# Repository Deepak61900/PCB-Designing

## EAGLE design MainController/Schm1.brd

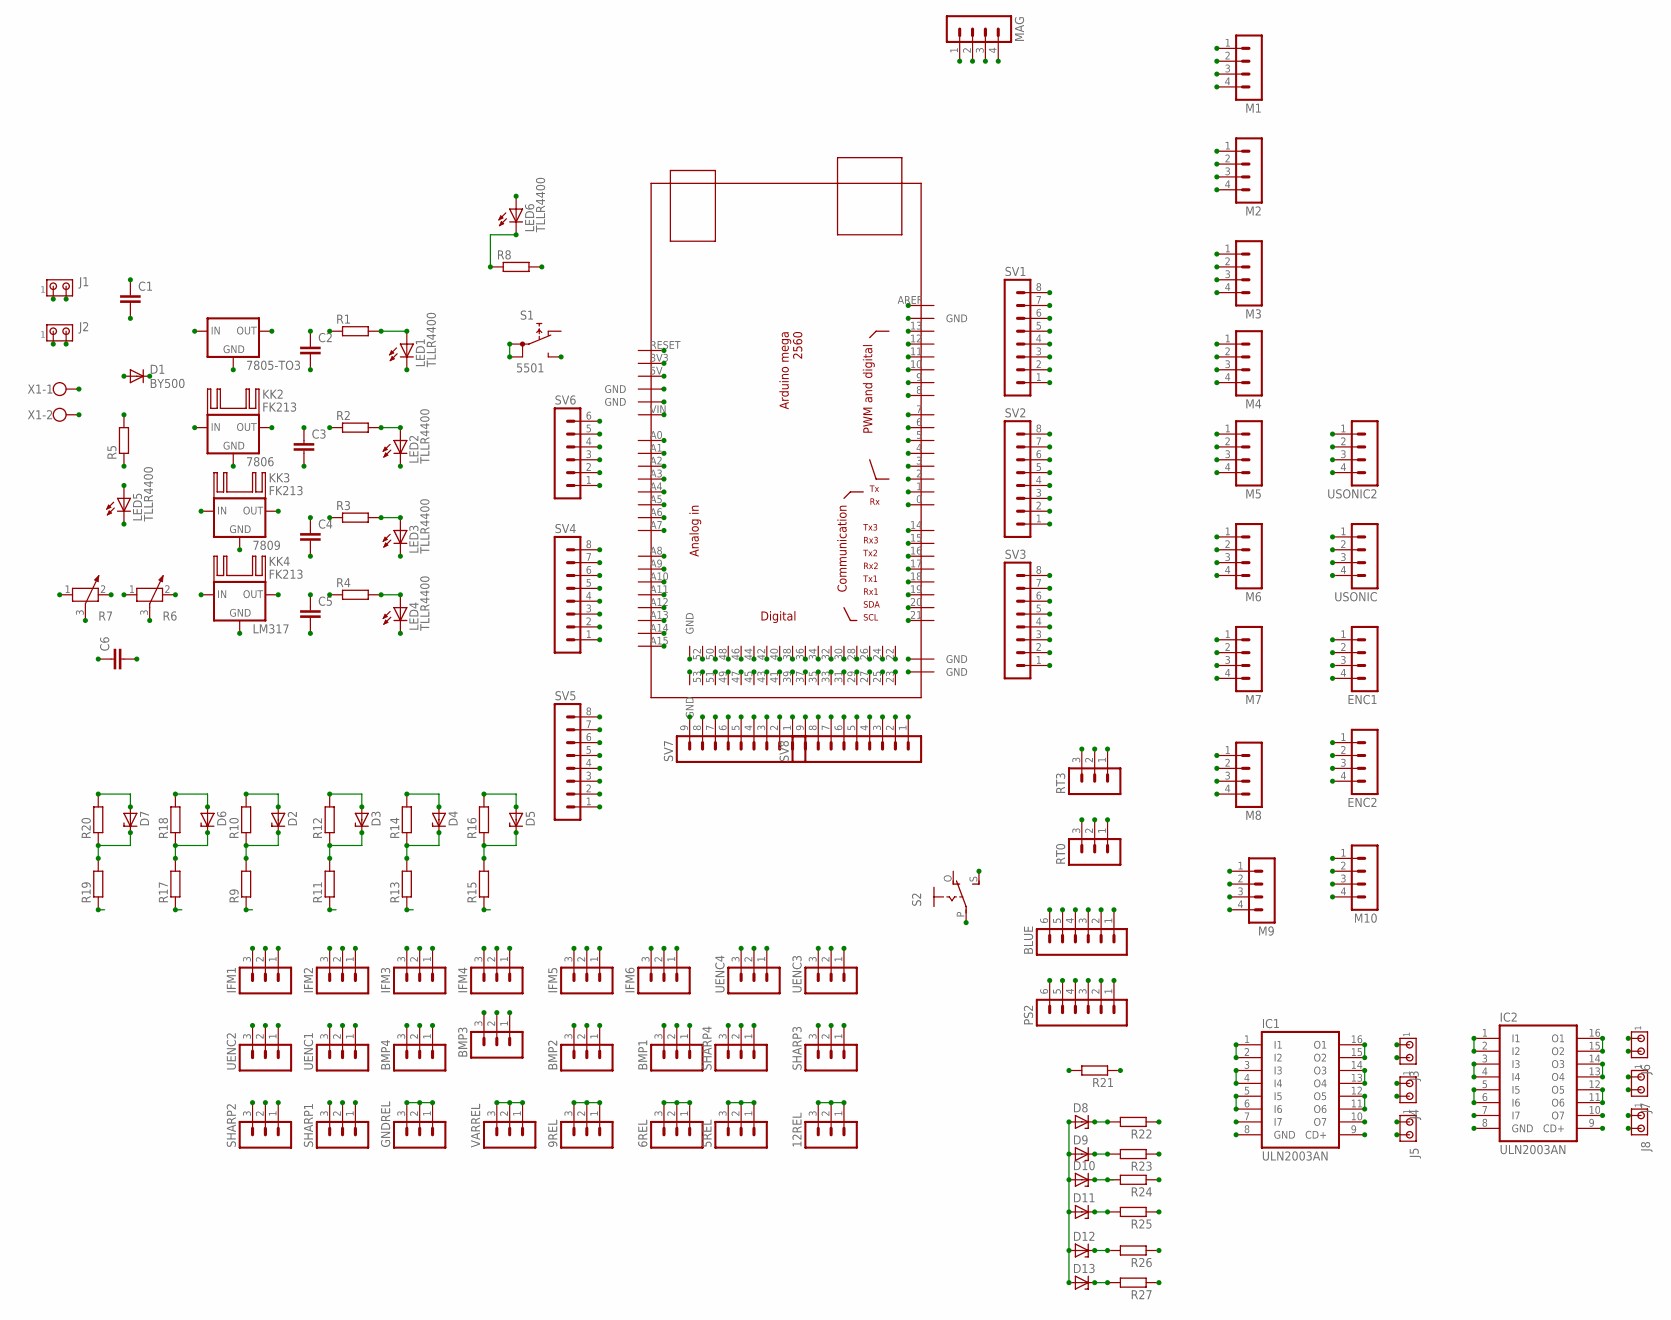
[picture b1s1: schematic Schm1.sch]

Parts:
5REL, 6REL, 9REL, 12REL: MA03-1
7805-TO3: 78XX-TO3; TO3-78
7806, 7809: 78XXS
BLUE: MA06-1
BMP1, BMP2, BMP3, BMP4: MA03-1
C1: C-EU075-063X106; C075-063X106
C2, C3, C4, C5, C6: C-EU050-075X075; C050-075X075
D1: BY500; DO201-15
D2, D3, D4, D5, D6, D7, D8, D9, D10, D11, D12, D13: ZENER-DIODEDO34-7; DO34Z7
ENC1, ENC2: MA04-1
GNDREL: MA03-1
IC1, IC2: ULN2003AN; DIL16
IFM1, IFM2, IFM3, IFM4, IFM5, IFM6: MA03-1
J1, J2: MTA02-156; 1X2MTA
J3, J4, J5, J6, J7, J8: MTA02-100; 10X02MTA
KK2, KK3, KK4: FK213
LED1, LED2, LED3, LED4, LED5, LED6: TLLR4400; LED3MM
LM317: 78XXS
M1, M2, M3, M4, M5, M6, M7, M8, M9, M10: MA04-1
MAG: MA04-1
PS2: MA06-1
R1, R2, R3, R4, R5, R8, R9, R10, R11, R12, R13, R14, R15, R16, R17, R18, R19, R20, R21, R22, R23, R24, R25, R26, R27: R-EU_0207/10; 0207/10
R6, R7: POTENTIOMETER_PT-10; PT-10
RT0, RT3: MA03-1
S1: 5501
S2: EG1218S; EG1218
SHARP1, SHARP2, SHARP3, SHARP4: MA03-1
SV1, SV2, SV3, SV4, SV5: MA08-1
SV6: MA06-1
SV7, SV8: MA09-1
U$1: MEGA_DEVICE; MEGABOX
UENC1, UENC2, UENC3, UENC4: MA03-1
USONIC, USONIC2: MA04-1
VARREL: MA03-1
X1: W237-102

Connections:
0: RT0.2, SV2.1, U$1.0
1: RT0.3, SV2.2, U$1.1
2: ENC1.1, SV2.3, U$1.2, UENC1.3
3: ENC1.2, SV2.4, U$1.3, UENC2.3
3V3: MAG.2, SV6.5, U$1.3V3
4: M1.1, SV2.5, U$1.4
5: M6.1, SV2.6, U$1.5
5OUT: 5REL.1, 5REL.2, 5REL.3, 7805-TO3.1 (OUT), BLUE.3, BMP1.2, BMP2.2, BMP3.2, BMP4.2, C2.1, ENC1.3, ENC2.3, PS2.2, R1.1, R21.1, SHARP1.1, SHARP2.1, SHARP3.1, SHARP4.1, UENC1.2, UENC2.2, UENC3.2, UENC4.2, USONIC.4, USONIC2.4
6: M7.1, SV2.7, U$1.6
6OUT: 6REL.1, 6REL.2, 6REL.3, 7806.OUT, C3.1, R2.1
7: M8.1, SV2.8, U$1.7
8: M9.1, SV1.1, U$1.8
9: M10.1, SV1.2, U$1.9
10: M5.1, SV1.3, U$1.10
11: M4.1, SV1.4, U$1.11
12: M3.1, SV1.5, U$1.12
12IN: 7805-TO3.2 (IN), 7806.IN, 7809.IN, C6.1, D1.C, LM317.IN
12V: 12REL.1, 12REL.2, 12REL.3, C1.1, D1.A, IC1.9 (CD+), IC2.9 (CD+), IFM1.2, IFM2.2, IFM3.2, IFM4.2, IFM5.2, IFM6.2, J1.1, J2.1, J3.1, J4.1, J5.1, J6.1, J7.1, J8.1, R5.2, X1.1
13: M2.1, SV1.6, U$1.13
14: RT3.3, SV3.8, U$1.14
15: RT3.2, SV3.7, U$1.15
16: BLUE.5, SV3.6, U$1.16
17: BLUE.4, SV3.5, U$1.17
18: ENC2.1, SV3.4, U$1.18, UENC3.3
19: ENC2.2, SV3.3, U$1.19, UENC4.3
20: MAG.3, SV3.2, U$1.20
21: MAG.4, SV3.1, U$1.21
22: M1.2, U$1.22
23: M1.3, SV8.2, U$1.23
24: M2.2, U$1.24
25: M6.2, SV8.3, U$1.25
26: M2.3, U$1.26
27: M6.3, SV8.4, U$1.27
28: M3.2, U$1.28
29: M7.2, SV8.5, U$1.29
30: M3.3, U$1.30
31: M7.3, SV8.6, U$1.31
32: M4.2, U$1.32
33: M8.2, SV8.7, U$1.33
34: M4.3, U$1.34
35: M8.3, SV8.8, U$1.35
36: M5.2, U$1.36
37: M9.2, SV8.9, U$1.37
38: M5.3, U$1.38
39: M9.3, SV7.1, U$1.39
40: BMP4.3, U$1.40
41: D11.C, R25.2, SV7.2, U$1.41
42: BMP2.3, U$1.42
43: D12.C, R26.2, SV7.3, U$1.43
44: BMP1.3, U$1.44
45: D13.C, R27.2, SV7.4, U$1.45
46: BMP3.3, U$1.46
47: PS2.6, SV7.5, U$1.47
48: D10.C, R24.2, U$1.48
49: PS2.5, SV7.6, U$1.49
50: D9.C, R23.2, U$1.50
51: PS2.4, SV7.7, U$1.51
52: D8.C, R22.2, U$1.52
53: PS2.3, R21.2, SV7.8, U$1.53
A0: M10.3, SV4.8, U$1.A0
A1: M10.2, SV4.7, U$1.A1
A2: SHARP1.3, SV4.6, U$1.A2
A3: SHARP2.3, SV4.5, U$1.A3
A4: SHARP3.3, SV4.4, U$1.A4
A5: SHARP4.3, SV4.3, U$1.A5
A6: SV4.2, U$1.A6, USONIC.3
A7: SV4.1, U$1.A7, USONIC.2
A8: SV5.8, U$1.A8, USONIC2.3
A9: SV5.7, U$1.A9, USONIC2.2
A10: D7.C, R19.2, R20.1, SV5.6, U$1.A10
A11: D6.C, R17.2, R18.1, SV5.5, U$1.A11
A12: D2.C, R9.2, R10.1, SV5.4, U$1.A12
A13: D3.C, R11.2, R12.1, SV5.3, U$1.A13
A14: D4.C, R13.2, R14.1, SV5.2, U$1.A14
A15: D5.C, R15.2, R16.1, SV5.1, U$1.A15
AREF: SV1.8, U$1.AREF
B3V3: BLUE.2, S2.P
DIN: LED5.A, R5.1
GND: 7805-TO3.3 (GND), 7806.GND, 7809.GND, BLUE.1, BMP1.1, BMP2.1, BMP3.1, BMP4.1, C1.2, C2.2, C3.2, C4.2, C5.2, C6.2, D2.A, D3.A, D4.A, D5.A, D6.A, D7.A, D8.A, D9.A, D10.A, D11.A, D12.A, D13.A, ENC1.4, ENC2.4, GNDREL.1, GNDREL.2, GNDREL.3, IC1.8 (GND), IC2.8 (GND), IFM1.1, IFM2.1, IFM3.1, IFM4.1, IFM5.1, IFM6.1, J1.2, J2.2, LED1.K (C), LED2.K (C), LED3.K (C), LED4.K (C), LED5.K (C), M1.4, M2.4, M3.4, M4.4, M5.4, M6.4, M7.4, M8.4, M9.4, M10.4, MAG.1, PS2.1, R7.3, R8.2, R10.2, R12.2, R14.2, R16.2, R18.2, R20.2, RT0.1, RT3.1, S1.NO, SHARP1.2, SHARP2.2, SHARP3.2, SHARP4.2, SV1.7, SV6.2, SV6.3, SV7.9, U$1.GND@1 (GND), U$1.GND@2 (GND), U$1.GND@3 (GND), U$1.GND@6 (GND), U$1.GND@7 (GND), UENC1.1, UENC2.1, UENC3.1, UENC4.1, USONIC.1, USONIC2.1, X1.2
JOK1: LM317.GND, R6.3, R7.1
KEY: BLUE.6, S2.S
unnamed: LED6.K (C), R8.1
unnamed: LED4.A, R4.2
unnamed: LED3.A, R3.2
unnamed: LED2.A, R2.2
unnamed: LED1.A, R1.2
PN1: IC1.15 (O2), IC1.16 (O1), J3.2
PN2: IC1.13 (O4), IC1.14 (O3), J4.2
PN3: IC1.11 (O6), IC1.12 (O5), J5.2
PN4: IC2.15 (O2), IC2.16 (O1), J6.2
PN5: IC2.13 (O4), IC2.14 (O3), J7.2
PN6: IC2.11 (O6), IC2.12 (O5), J8.2
RESET: S1.1A, S1.1B, SV6.6, U$1.RESET
S1: IFM1.3, R19.1
S2: IFM2.3, R17.1
S3: IFM3.3, R9.1
S4: IFM4.3, R11.1
S5: IFM5.3, R13.1
S6: IFM6.3, R15.1
U1: IC1.5 (I5), IC1.6 (I6), R22.1
U2: IC1.3 (I3), IC1.4 (I4), R23.1
U3: IC1.1 (I1), IC1.2 (I2), R24.1
U4: IC2.5 (I5), IC2.6 (I6), R25.1
U5: IC2.3 (I3), IC2.4 (I4), R26.1
U6: IC2.1 (I1), IC2.2 (I2), R27.1
VAROUT: C5.1, LM317.OUT, R4.1, R6.1, VARREL.1, VARREL.2, VARREL.3
VCC: LED6.A, SV6.4, SV8.1, U$1.5V, U$1.GND@4 (GND), U$1.GND@5 (GND)
VIN: 9REL.1, 9REL.2, 9REL.3, 7809.OUT, C4.1, R3.1, SV6.1, U$1.VIN

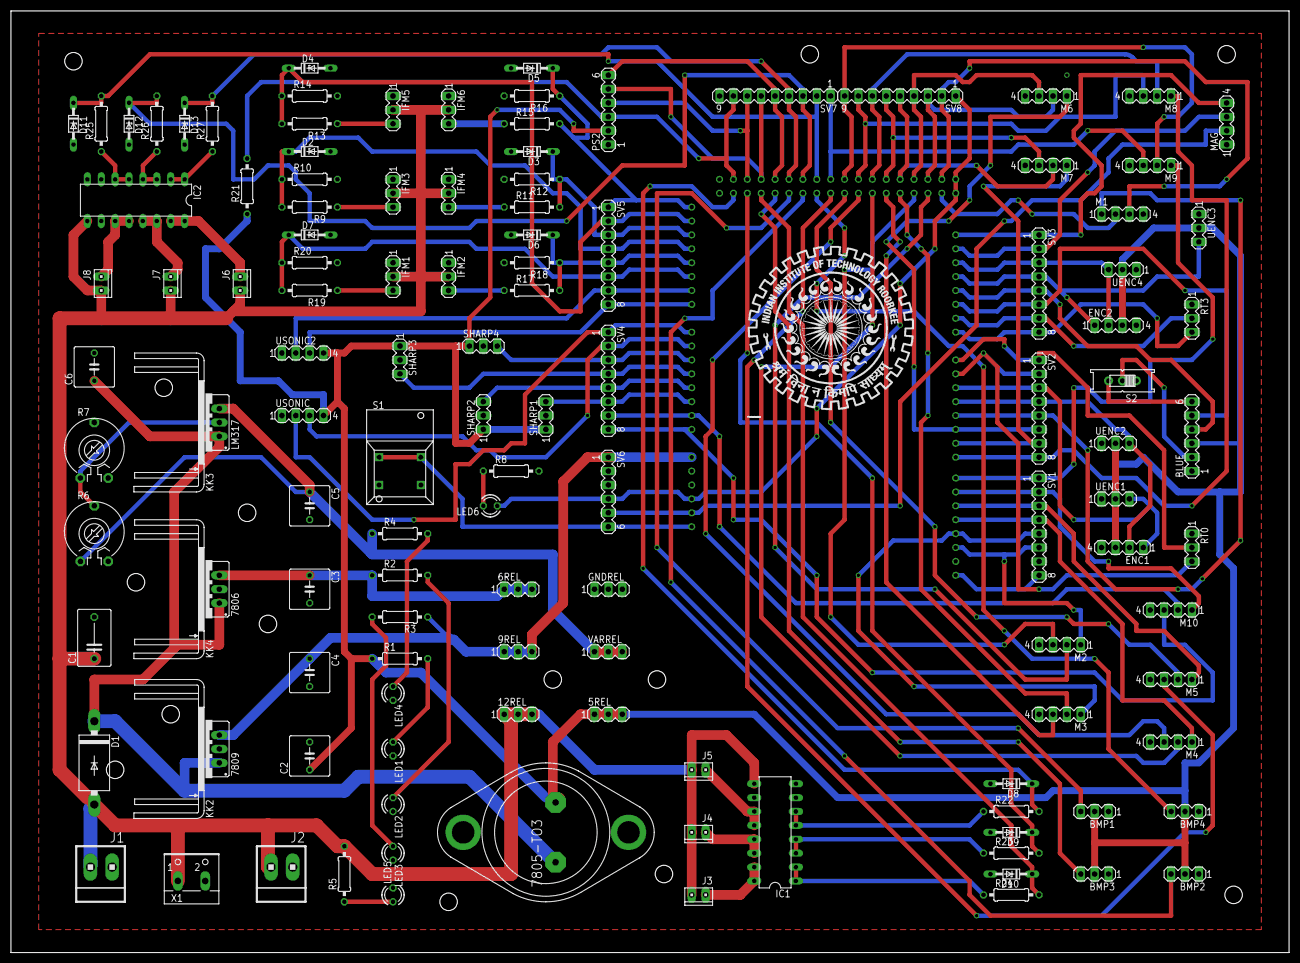
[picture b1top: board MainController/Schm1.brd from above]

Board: 2 copper layers, 233.7 x 172.1 mm, 125 parts (1 on the bottom side), 108 nets.

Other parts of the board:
U$2: IITR_2

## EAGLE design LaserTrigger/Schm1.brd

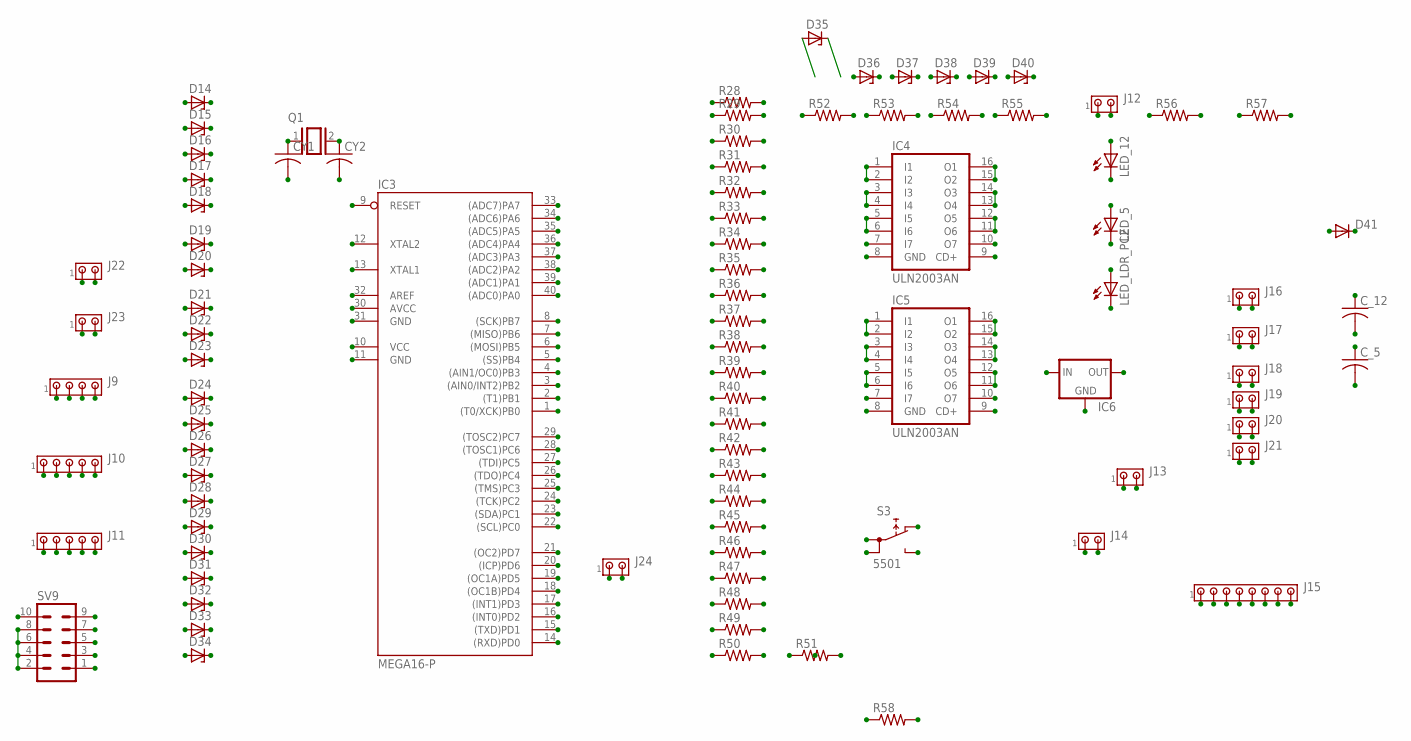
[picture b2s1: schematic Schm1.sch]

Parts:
CY1, CY2: C-US050-024X044; C050-024X044
C_5, C_12: C-US050-075X075; C050-075X075
D14, D15, D16, D17, D18, D19, D20, D21, D22, D23, D24, D25, D26, D27, D28, D29, D30, D31, D32, D33, D34, D35, D36, D37, D38, D39, D40: ZENER-DIODEDO34-7; DO34Z7
D41: DIODE-DO201-15; DO201-15
IC3: MEGA16-P; DIL40
IC4, IC5: ULN2003AN; DIL16
IC6: 78XX-TO3; TO3-78
J9: MTA04-100; 10X04MTA
J10, J11: MTA05-100; 10X05MTA
J12, J13, J23: MTA02-156; 1X2MTA
J14, J16, J17, J18, J19, J20, J21, J22, J24: MTA02-100; 10X02MTA
J15: MTA08-100; 10X08MTA
LED_5, LED_12: LED3MM
LED_LDR_PC2: LED3MM
Q1: XTAL/S; QS
R28, R29, R30, R31, R32, R33, R34, R35, R36, R37, R38, R39, R40, R41, R42, R43, R44, R45, R46, R47, R48, R49, R50, R51, R52, R53, R54, R55, R56, R57, R58: R-US_0207/7; 0207/7
S3: 5501
SV9: MA05-2

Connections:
12V1: C_12.1, D41.C, IC4.9 (CD+), IC5.9 (CD+), IC6.2 (IN), J12.1, J16.2, J17.2, J18.2, J19.2, J20.2, J21.2, J22.1, R28.2, R29.2, R30.2, R31.2, R32.2, R33.2, R34.2, R35.2, R36.2, R37.2, R38.2, R39.2, R40.2, R41.2, R42.2, R43.2, R44.2, R45.2, R46.2, R47.2, R48.2, R49.2
AREF1: IC3.32 (AREF)
D: D41.A, J23.1
GND1: CY1.2, CY2.2, C_5.2, C_12.2, D14.A, D15.A, D16.A, D17.A, D18.A, D19.A, D20.A, D21.A, D22.A, D23.A, D24.A, D25.A, D26.A, D27.A, D28.A, D29.A, D30.A, D31.A, D32.A, D33.A, D34.A, D35.A, D36.A, D37.A, D38.A, D39.A, D40.A, IC3.11 (GND), IC3.31 (GND), IC4.8 (GND), IC5.8 (GND), IC6.3 (GND), J9.4, J12.2, J13.2, J14.2, J22.2, J23.2, LED_5.K (C), LED_12.K (C), LED_LDR_PC2.K (C), S3.NO, SV9.2, SV9.4, SV9.6, SV9.8
LED1: LED_12.A, R49.1
LED2: LED_5.A, R50.1
LED3: LED_LDR_PC2.A, R51.2
N1: IC4.15 (O2), IC4.16 (O1), J16.1
N2: IC4.13 (O4), IC4.14 (O3), J17.1
N3: IC4.11 (O6), IC4.12 (O5), J18.1
N4: IC5.15 (O2), IC5.16 (O1), J19.1
N5: IC5.13 (O4), IC5.14 (O3), J20.1
N6: IC5.11 (O6), IC5.12 (O5), J21.1
PA0: D34.C, IC3.40 ((ADC0)PA0), J15.1, R48.1
PA1: D33.C, IC3.39 ((ADC1)PA1), J15.2, R47.1
PA2: D32.C, IC3.38 ((ADC2)PA2), J15.3, R46.1
PA3: D31.C, IC3.37 ((ADC3)PA3), J15.4, R45.1
PA4: D30.C, IC3.36 ((ADC4)PA4), J15.5, R44.1
PA5: D29.C, IC3.35 ((ADC5)PA5), J15.6, R43.1
PA6: D28.C, IC3.34 ((ADC6)PA6), J15.7, R42.1
PA7: D27.C, IC3.33 ((ADC7)PA7), J15.8, R41.1
PB0: D14.C, IC3.1 ((T0/XCK)PB0), J10.1, R28.1
PB1: D15.C, IC3.2 ((T1)PB1), J10.2, R29.1
PB2: D16.C, IC3.3 ((AIN0/INT2)PB2), J10.3, R30.1
PB3: D17.C, IC3.4 ((AIN1/OC0)PB3), J10.4, R31.1
PB4: D18.C, IC3.5 ((SS)PB4), J10.5, R32.1
PB5: IC3.6 ((MOSI)PB5), SV9.9
PB6: IC3.7 ((MISO)PB6), SV9.1
PB7: IC3.8 ((SCK)PB7), SV9.3
PC0: D25.C, IC3.22 ((SCL)PC0), J9.2, R39.1
PC1: D26.C, IC3.23 ((SDA)PC1), J9.1, R40.1
PC2: D40.C, IC3.24 ((TCK)PC2), R51.1, R57.1
PC3: D39.C, IC3.25 ((TMS)PC3), R56.1
PC4: D38.C, IC3.26 ((TDO)PC4), R55.1
PC5: D37.C, IC3.27 ((TDI)PC5), R54.1
PC6: D36.C, IC3.28 ((TOSC1)PC6), R53.1
PC7: D35.C, IC3.29 ((TOSC2)PC7), R52.1
PD0: IC3.14 ((RXD)PD0), J24.1
PD1: IC3.15 ((TXD)PD1), J24.2
PD2: D19.C, IC3.16 ((INT0)PD2), J11.1, R33.1
PD3: D20.C, IC3.17 ((INT1)PD3), J11.2, R34.1
PD4: D21.C, IC3.18 ((OC1B)PD4), J11.3, R35.1
PD5: D22.C, IC3.19 ((OC1A)PD5), J11.4, R36.1
PD6: D23.C, IC3.20 ((ICP)PD6), J11.5, R37.1
PD7: D24.C, IC3.21 ((OC2)PD7), J9.3, R38.1
RESET1: IC3.9 (RESET), R58.2, S3.1A, S3.1B, SV9.5
U7: IC4.1 (I1), IC4.2 (I2), R52.2
U8: IC4.3 (I3), IC4.4 (I4), R53.2
U9: IC4.5 (I5), IC4.6 (I6), R54.2
U10: IC5.1 (I1), IC5.2 (I2), R55.2
U11: IC5.3 (I3), IC5.4 (I4), R56.2
U12: IC5.5 (I5), IC5.6 (I6), R57.2
VCC1: C_5.1, IC3.10 (VCC), IC3.30 (AVCC), IC6.1 (OUT), J13.1, J14.1, R50.2, R58.1, SV9.10
XTAL1: CY1.1, IC3.13 (XTAL1), Q1.1
XTAL2: CY2.1, IC3.12 (XTAL2), Q1.2

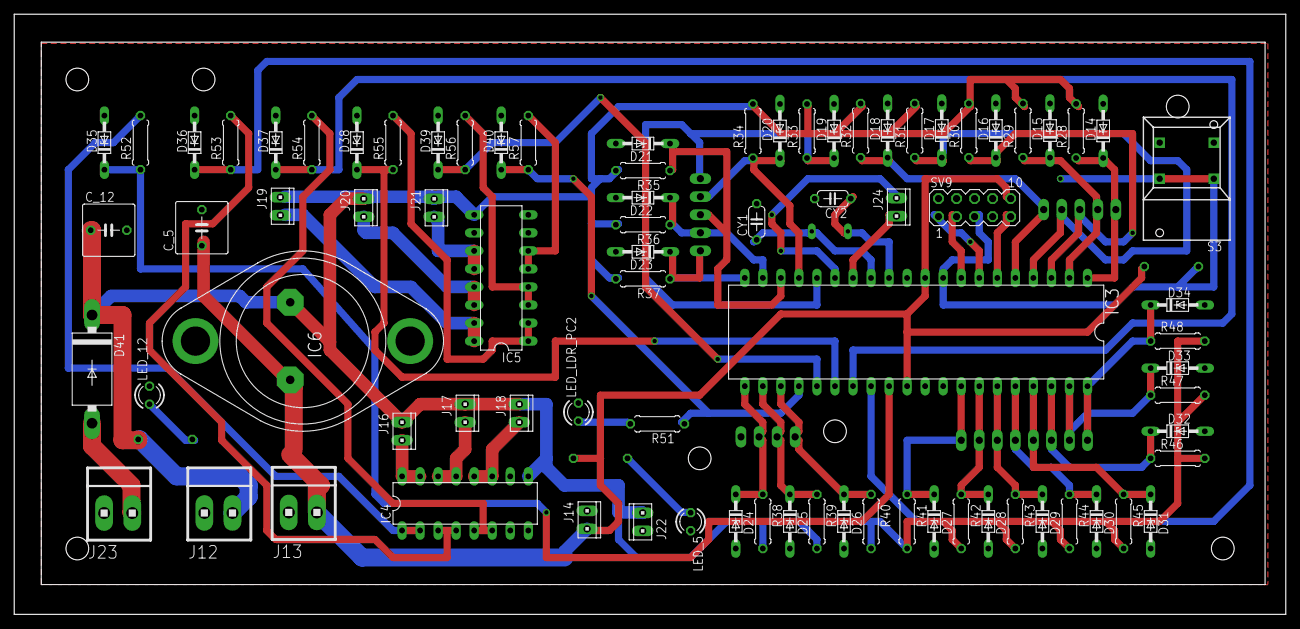
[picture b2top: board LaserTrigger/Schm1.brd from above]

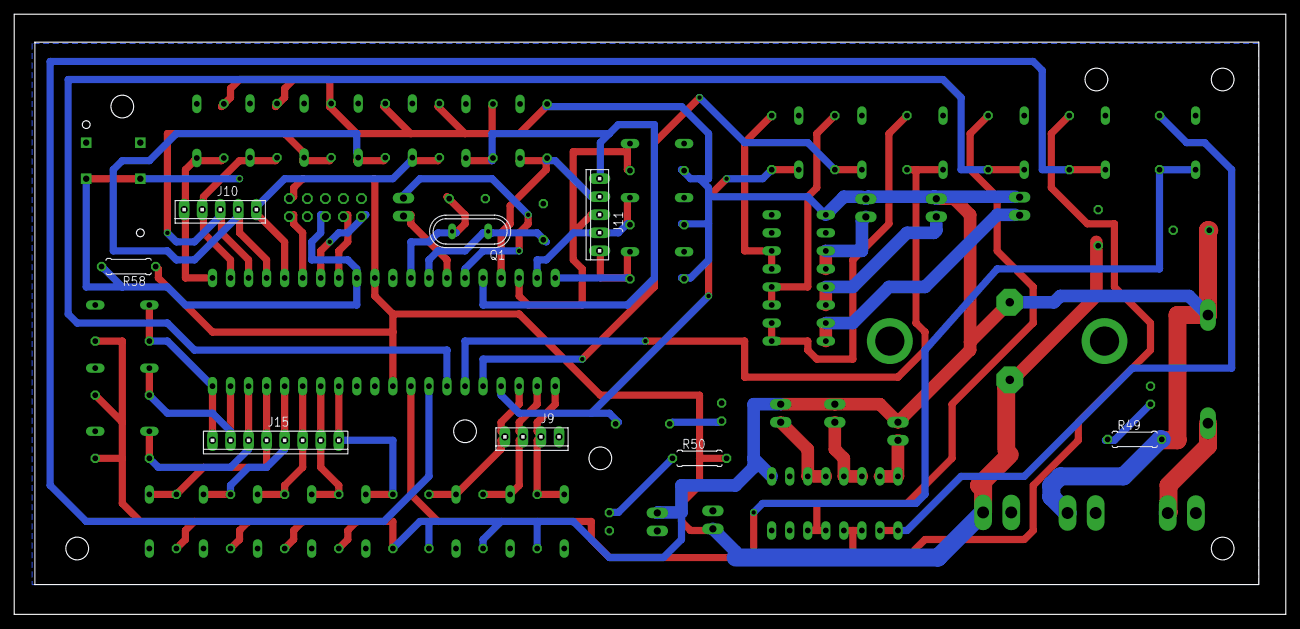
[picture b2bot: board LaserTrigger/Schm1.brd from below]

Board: 2 copper layers, 179.0 x 84.5 mm, 89 parts (8 on the bottom side), 54 nets.

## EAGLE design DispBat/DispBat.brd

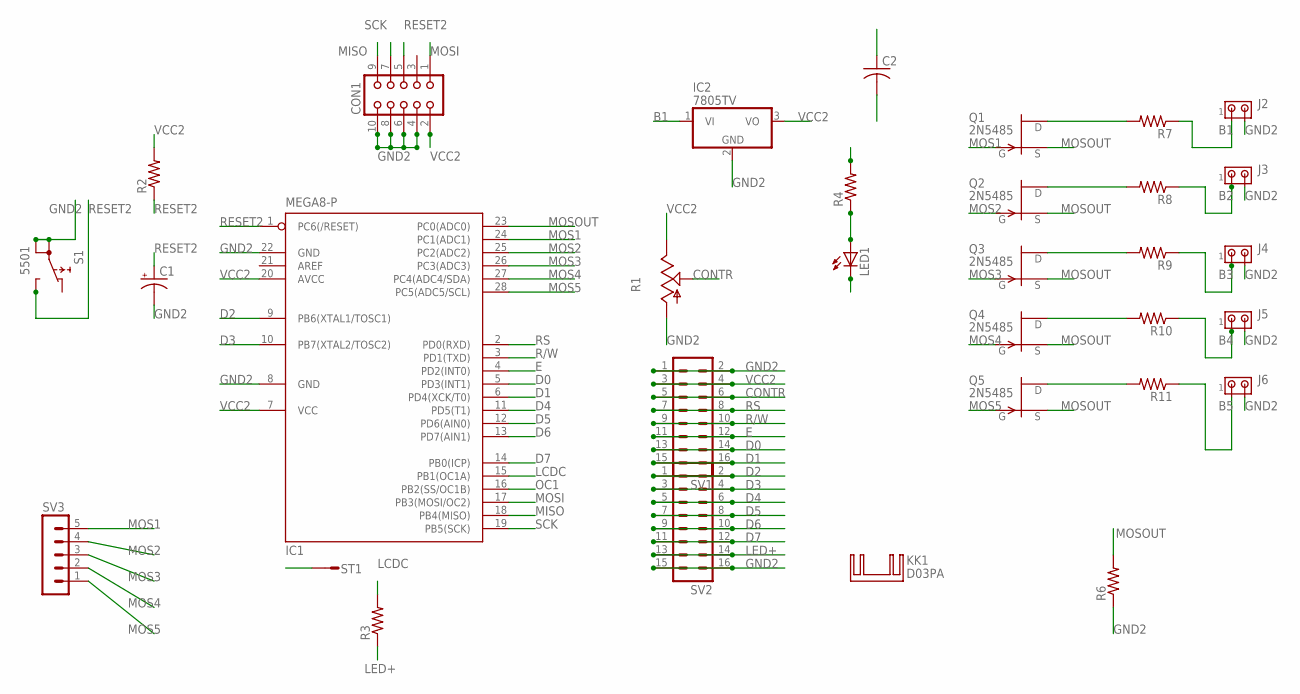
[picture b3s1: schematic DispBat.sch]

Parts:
C1: CPOL-USE2.5-7; E2,5-7
C2: C-US075-042X103; C075-042X103
CON1: CON10
IC1: MEGA8-P; DIL28-3
IC2: 7805TV; TO220V
J2, J3, J4, J5, J6: MTA02-156; 1X2MTA
KK1: D03PA
LED1: LED_ELD260; LED_LD260
Q1, Q2, Q3, Q4, Q5: 2N5485; TO92-
R1: TRIM_US-CA9V; CA9V
R2, R3, R4, R6, R7, R8, R9, R10, R11: R-US_0207/10; 0207/10
S1: 5501
ST1: ST2,8
SV1, SV2: MA08-2
SV3: MA05-1

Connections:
B1: IC2.1 (VI), J2.1, R7.1
B2: J3.1, R8.1
B3: J4.1, R9.1
B4: J5.1, R10.1
B5: J6.1, R11.1
CONTR: R1.S, SV1.5, SV1.6
D0: IC1.5 (PD3(INT1)), SV1.13, SV1.14
D1: IC1.6 (PD4(XCK/T0)), SV1.15, SV1.16
D2: IC1.9 (PB6(XTAL1/TOSC1)), SV2.1, SV2.2
D3: IC1.10 (PB7(XTAL2/TOSC2)), SV2.3, SV2.4
D4: IC1.11 (PD5(T1)), SV2.5, SV2.6
D5: IC1.12 (PD6(AIN0)), SV2.7, SV2.8
D6: IC1.13 (PD7(AIN1)), SV2.9, SV2.10
D7: IC1.14 (PB0(ICP)), SV2.11, SV2.12
E: IC1.4 (PD2(INT0)), SV1.11, SV1.12
GND2: C1.-, C2.2, CON1.4, CON1.6, CON1.8, CON1.10, IC1.8 (GND), IC1.22 (GND), IC2.2 (GND), J2.2, J3.2, J4.2, J5.2, J6.2, LED1.K (C), R1.A, R6.1, S1.1A, S1.1B, SV1.1, SV1.2, SV2.15, SV2.16
LCDC: IC1.15 (PB1(OC1A)), R3.2
LED+: R3.1, SV2.13, SV2.14
MISO: CON1.9, IC1.18 (PB4(MISO))
MOS1: IC1.24 (PC1(ADC1)), Q1.1 (G), SV3.5
MOS2: IC1.25 (PC2(ADC2)), Q2.1 (G), SV3.4
MOS3: IC1.26 (PC3(ADC3)), Q3.1 (G), SV3.3
MOS4: IC1.27 (PC4(ADC4/SDA)), Q4.1 (G), SV3.2
MOS5: IC1.28 (PC5(ADC5/SCL)), Q5.1 (G), SV3.1
MOSI: CON1.1, IC1.17 (PB3(MOSI/OC2))
MOSOUT: IC1.23 (PC0(ADC0)), Q1.2 (S), Q2.2 (S), Q3.2 (S), Q4.2 (S), Q5.2 (S), R6.2
unnamed: LED1.A, R4.1
unnamed: Q1.3 (D), R7.2
unnamed: Q2.3 (D), R8.2
unnamed: Q3.3 (D), R9.2
unnamed: Q4.3 (D), R10.2
unnamed: Q5.3 (D), R11.2
OC1: IC1.16 (PB2(SS/OC1B)), ST1.1
R/W: IC1.3 (PD1(TXD)), SV1.9, SV1.10
RESET2: C1.+, CON1.5, IC1.1 (PC6(/RESET)), R2.1, S1.NO
RS: IC1.2 (PD0(RXD)), SV1.7, SV1.8
SCK: CON1.7, IC1.19 (PB5(SCK))
VCC2: C2.1, CON1.2, IC1.7 (VCC), IC1.20 (AVCC), IC2.3 (VO), R1.E, R2.2, R4.2, SV1.3, SV1.4

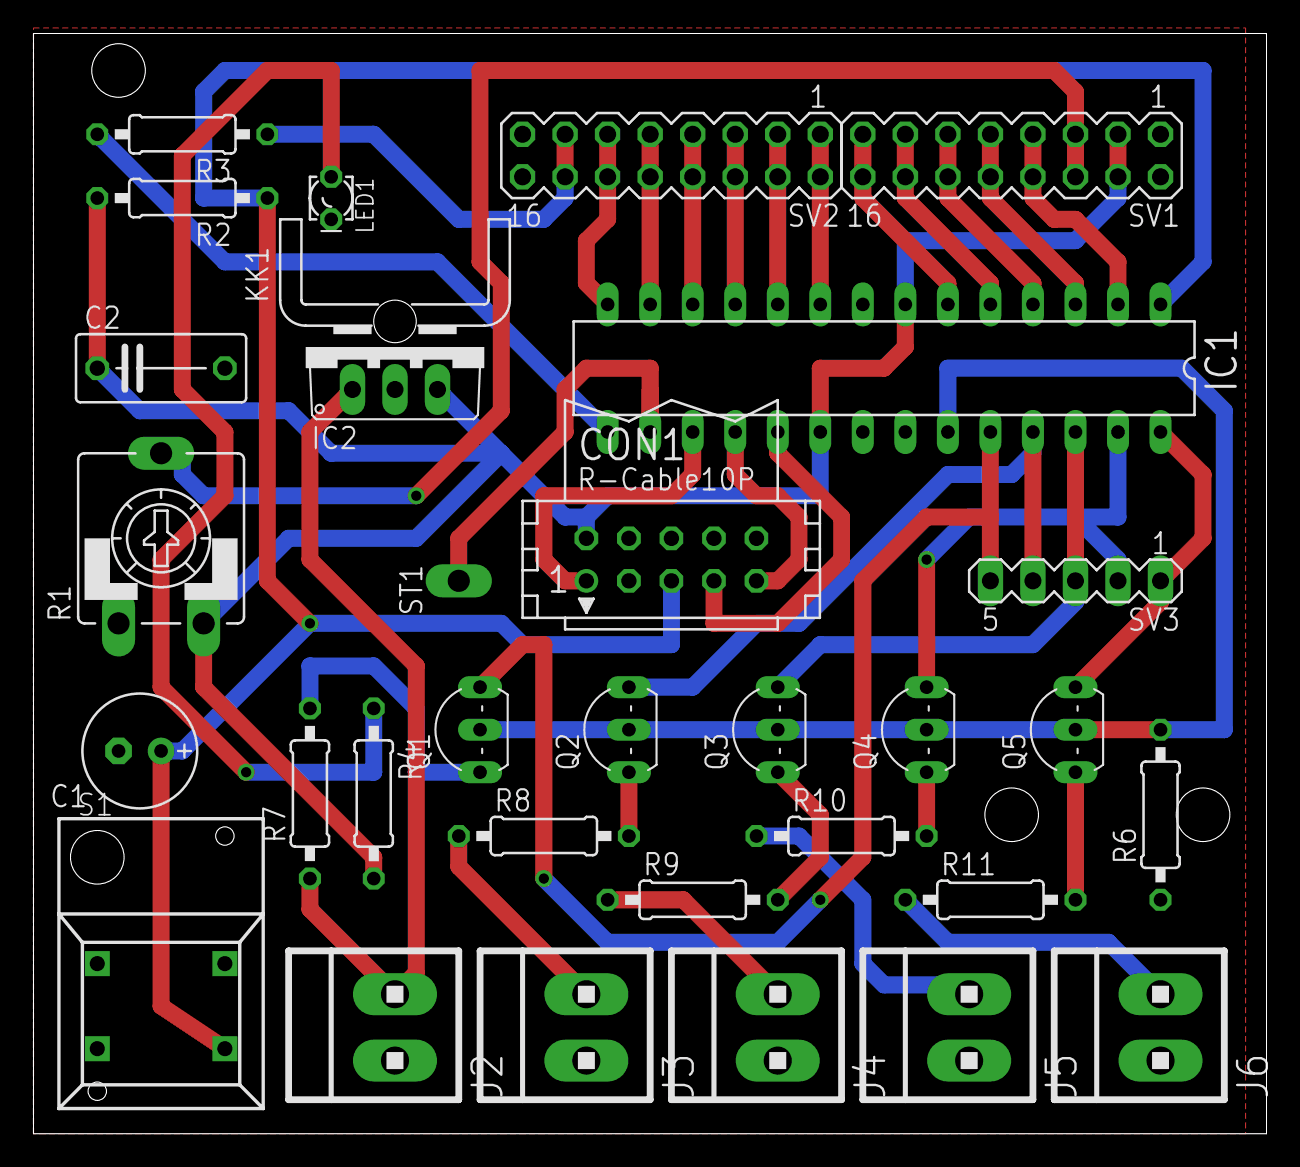
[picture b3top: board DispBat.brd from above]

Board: 2 copper layers, 73.6 x 65.7 mm, 32 parts (0 on the bottom side), 38 nets.

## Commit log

2015-02-20 First addition
